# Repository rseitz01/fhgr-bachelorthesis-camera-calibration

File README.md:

# fhgr-bachelorthesis-camera-calibration

## Ordnerstruktur

- [`doc`](doc) Allgemeine Dokumentationen
- [`ledrunner`](ledrunner) Alles bezüglich STM32 (HW, SW, ...)
- [`src`](src) Source Codes (PC)

Die Veröffentlichung der Bachelorarbeit auf GitHub wurde durch den Dozenten und den Auftraggeber nach der Präsentation erlaubt.

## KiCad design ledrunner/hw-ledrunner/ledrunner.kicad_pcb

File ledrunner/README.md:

# ledrunner

## Ordnerstruktur

- [`housing-ledrunner`](housing-ledrunner) Komplettes Gehäuse für die Hardware
- [`hw-ledrunner`](hw-ledrunner) Schema + PCB der Hardware
- [`sw-camera-calibration`](sw-camera-calibration) STM32 Software (Prototyp der Kalibration)
- [`sw-ledrunner`](sw-ledrunner) STM32 Software zur Hardware

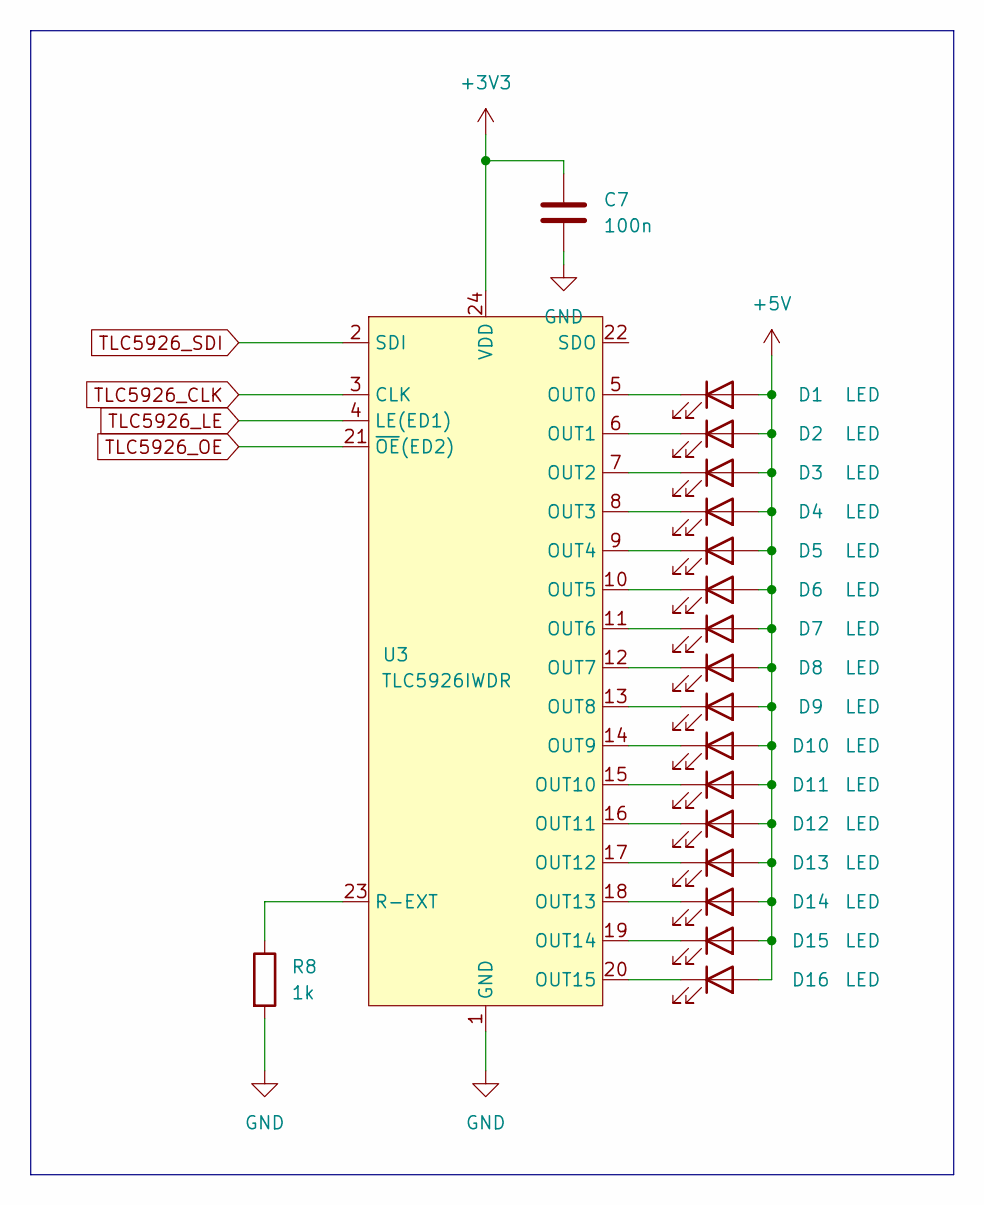
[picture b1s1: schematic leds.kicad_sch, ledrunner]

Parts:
C7: 100n; C_0603_1608Metric_Pad1.08x0.95mm_HandSolder
D1, D2, D3, D4, D5, D6, D7, D8, D9, D10, D11, D12, D13, D14, D15, D16: LED; LED_D5.0mm_FlatTop
R8: 1k; R_0603_1608Metric_Pad0.98x0.95mm_HandSolder
U3: TLC5926IWDR; SOIC-24W_7.5x15.4mm_P1.27mm

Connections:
+5V: D1.2 (A), D2.2 (A), D3.2 (A), D4.2 (A), D5.2 (A), D6.2 (A), D7.2 (A), D8.2 (A), D9.2 (A), D10.2 (A), D11.2 (A), D12.2 (A), D13.2 (A), D14.2 (A), D15.2 (A), D16.2 (A); also elsewhere on the board
GND: C7.2, R8.2, U3.1 (GND); also elsewhere on the board
unnamed: D1.1 (K), U3.5 (OUT0)
unnamed: D2.1 (K), U3.6 (OUT1)
unnamed: D3.1 (K), U3.7 (OUT2)
unnamed: D4.1 (K), U3.8 (OUT3)
unnamed: D5.1 (K), U3.9 (OUT4)
unnamed: D6.1 (K), U3.10 (OUT5)
unnamed: D7.1 (K), U3.11 (OUT6)
unnamed: D8.1 (K), U3.12 (OUT7)
unnamed: D9.1 (K), U3.13 (OUT8)
unnamed: D10.1 (K), U3.14 (OUT9)
unnamed: D11.1 (K), U3.15 (OUT10)
unnamed: D12.1 (K), U3.16 (OUT11)
unnamed: D13.1 (K), U3.17 (OUT12)
unnamed: D14.1 (K), U3.18 (OUT13)
unnamed: D15.1 (K), U3.19 (OUT14)
unnamed: D16.1 (K), U3.20 (OUT15)
unnamed: R8.1, U3.23 (R-EXT)
TLC5926_CLK: U3.3 (CLK); also elsewhere on the board
TLC5926_LE: U3.4 (LE(ED1)); also elsewhere on the board
TLC5926_OE: U3.21 (~OE(ED2)); also elsewhere on the board
TLC5926_SDI: U3.2 (SDI); also elsewhere on the board

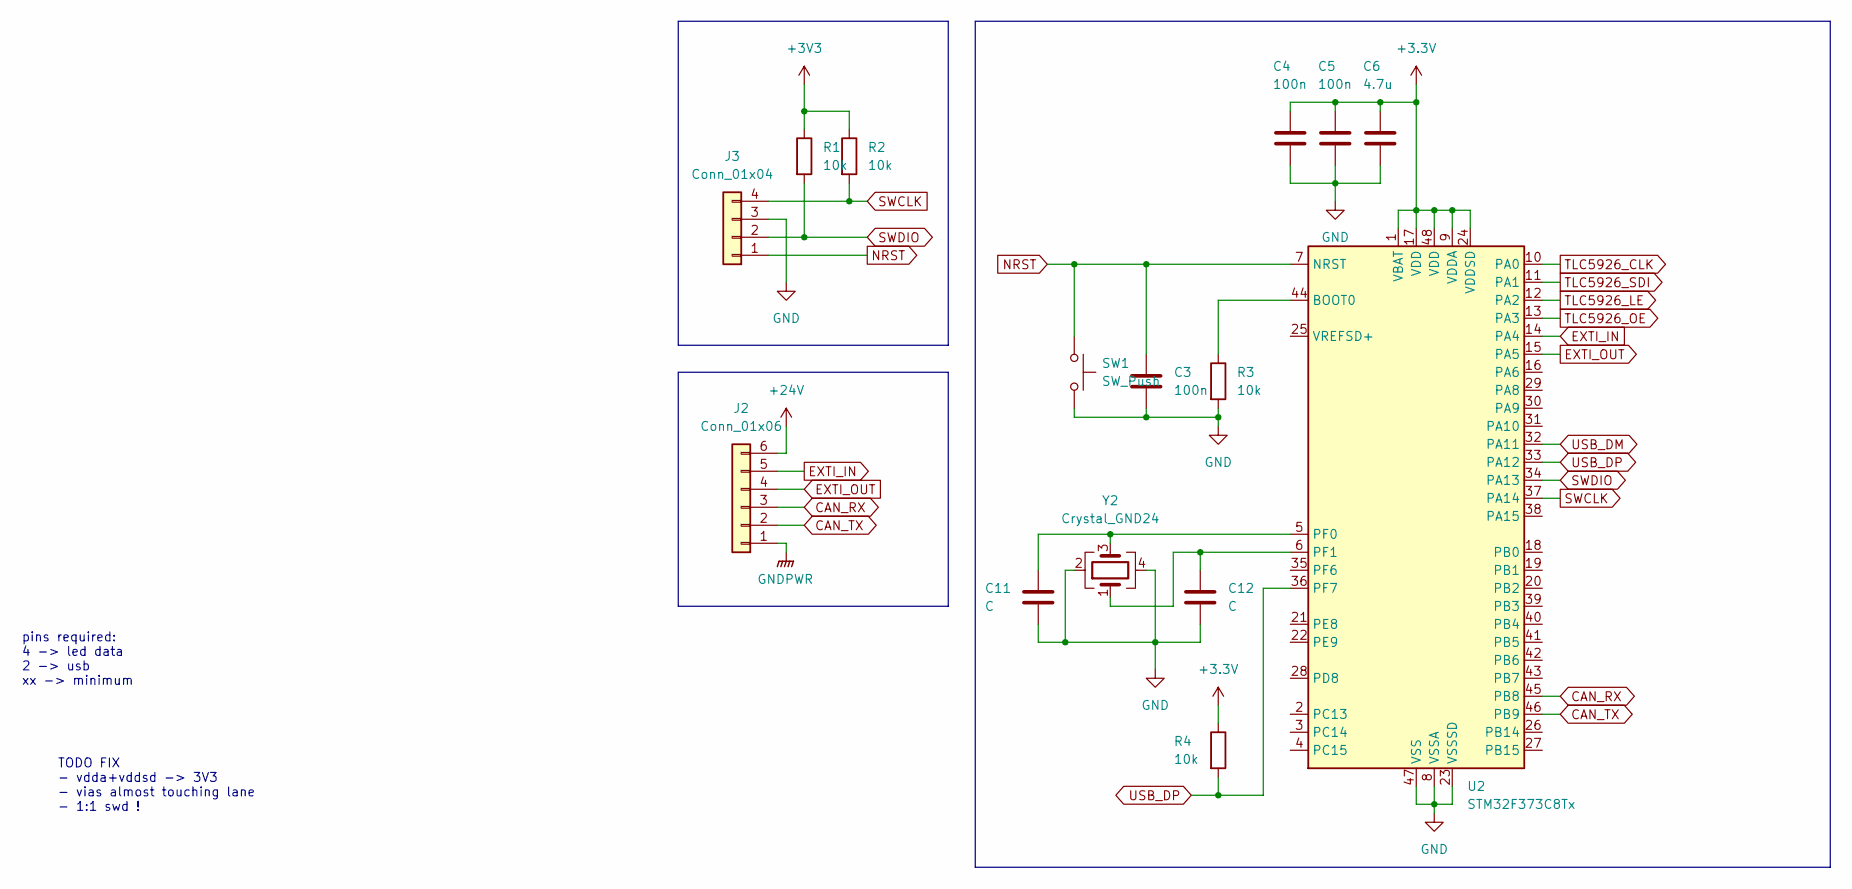
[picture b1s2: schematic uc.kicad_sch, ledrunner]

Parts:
C3, C4, C5: 100n; C_0603_1608Metric_Pad1.08x0.95mm_HandSolder
C6: 4.7u; C_0603_1608Metric_Pad1.08x0.95mm_HandSolder
C11, C12: C; C_0603_1608Metric_Pad1.08x0.95mm_HandSolder
J2: Conn_01x06; PinHeader_1x06_P2.54mm_Horizontal
J3: Conn_01x04; PinHeader_1x04_P2.54mm_Horizontal
R1, R2, R3, R4: 10k; R_0603_1608Metric_Pad0.98x0.95mm_HandSolder
SW1: SW_Push; SW_Push_1P1T_NO_6x6mm_H9.5mm
U2: STM32F373C8Tx; LQFP-48_7x7mm_P0.5mm
Y2: Crystal_GND24; Crystal_SMD_3225-4Pin_3.2x2.5mm

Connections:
+24V: J2.6; also elsewhere on the board
CAN_RX: J2.3, U2.45 (PB8)
CAN_TX: J2.2, U2.46 (PB9)
EXTI_IN: J2.5, U2.14 (PA4)
EXTI_OUT: J2.4, U2.15 (PA5)
GND: C3.2, C4.2, C5.2, C6.2, C11.2, C12.2, J3.3, R3.2, SW1.2, U2.8 (VSSA), U2.23 (VSSSD), U2.47 (VSS), Y2.2, Y2.4; also elsewhere on the board
GNDPWR: J2.1; also elsewhere on the board
NRST: C3.1, J3.1, SW1.1, U2.7 (NRST)
unnamed: R3.1, U2.44 (BOOT0)
unnamed: C11.1, U2.5 (PF0), Y2.3
unnamed: C12.1, U2.6 (PF1), Y2.1
SWCLK: J3.4, R2.2, U2.37 (PA14)
SWDIO: J3.2, R1.2, U2.34 (PA13)
TLC5926_CLK: U2.10 (PA0); also elsewhere on the board
TLC5926_LE: U2.12 (PA2); also elsewhere on the board
TLC5926_OE: U2.13 (PA3); also elsewhere on the board
TLC5926_SDI: U2.11 (PA1); also elsewhere on the board
USB_DM: U2.32 (PA11); also elsewhere on the board
USB_DP: R4.2, U2.33 (PA12), U2.36 (PF7); also elsewhere on the board

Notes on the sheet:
pins required: 4 -> led data 2 -> usb xx -> minimum
TODO FIX - vdda+vddsd -> 3V3 - vias almost touching lane - 1:1 swd !

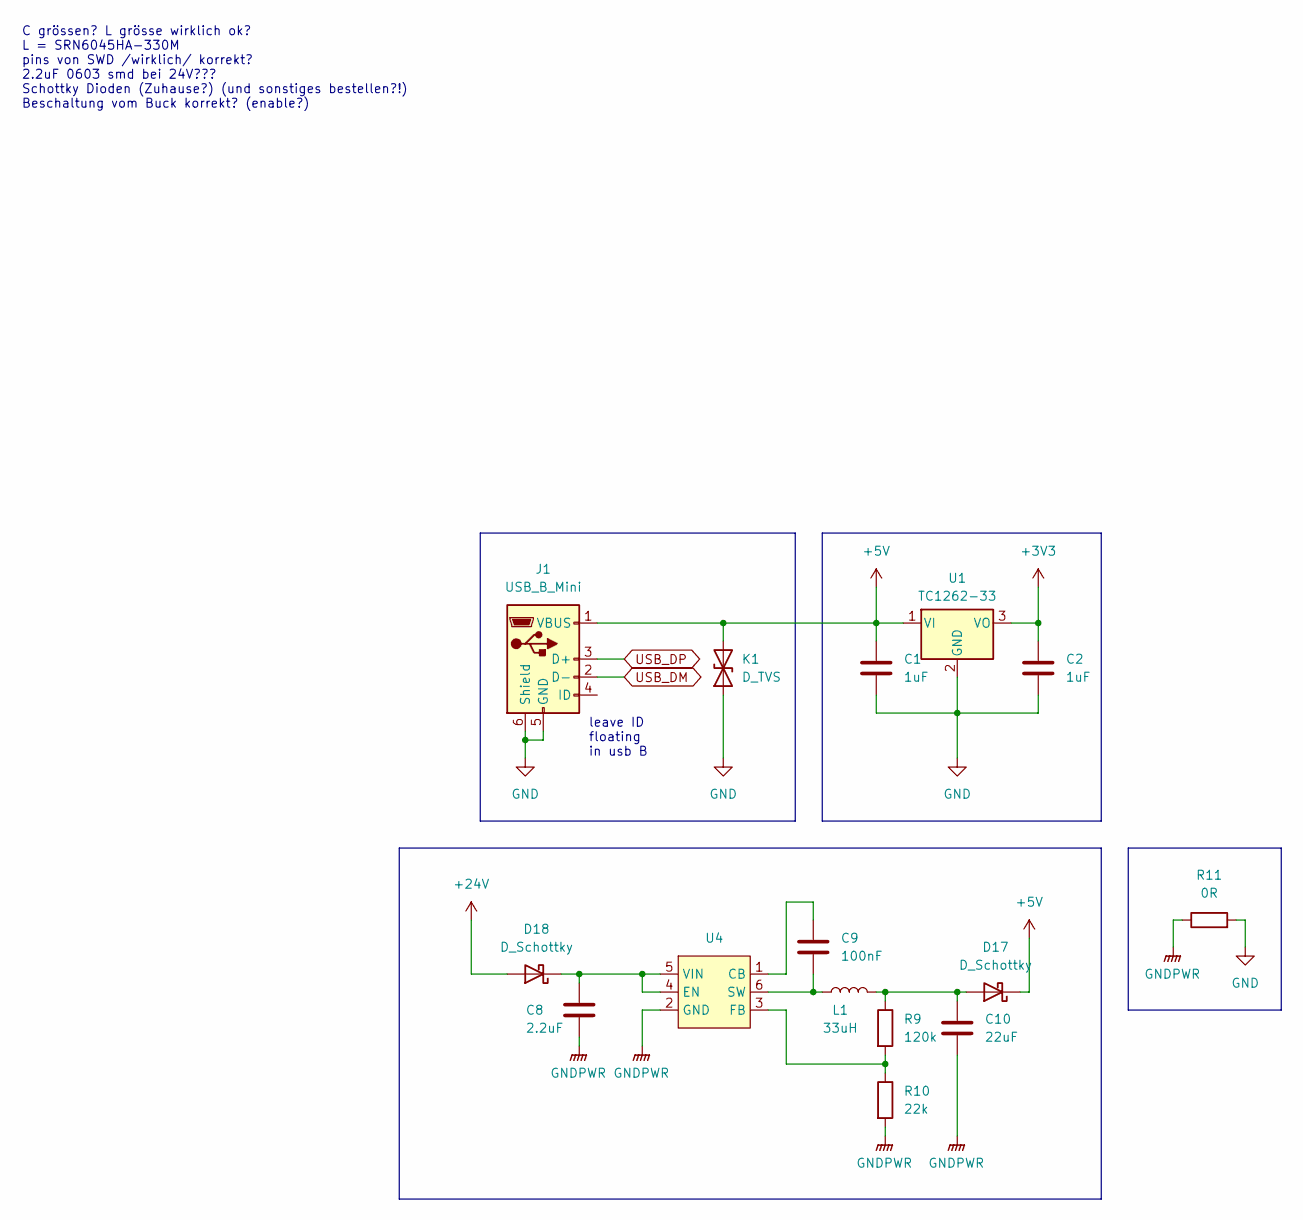
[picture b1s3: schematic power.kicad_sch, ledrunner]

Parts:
C1, C2: 1uF; C_0603_1608Metric_Pad1.08x0.95mm_HandSolder
C8: 2.2uF; C_0603_1608Metric_Pad1.08x0.95mm_HandSolder
C9: 100nF; C_0603_1608Metric_Pad1.08x0.95mm_HandSolder
C10: 22uF; C_Elec_5x5.4
D17, D18: D_Schottky; D_SMB
J1: USB_B_Mini; USB_Mini-B_Wuerth_65100516121_Horizontal
K1: D_TVS; D_SMB_Handsoldering
L1: 33uH; L_6.3x6.3_H3
R9: 120k; R_0603_1608Metric_Pad0.98x0.95mm_HandSolder
R10: 22k; R_0603_1608Metric_Pad0.98x0.95mm_HandSolder
R11: 0R; R_0603_1608Metric_Pad0.98x0.95mm_HandSolder
U1: TC1262-33; SOT-223-3_TabPin2
U4: SOT-23-6

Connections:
+5V: C1.1, D17.1 (K), J1.1 (VBUS), K1.2 (A2), U1.1 (VI); also elsewhere on the board
+24V: D18.2 (A); also elsewhere on the board
GND: C1.2, C2.2, J1.5 (GND), J1.6 (Shield), K1.1 (A1), R11.2, U1.2 (GND); also elsewhere on the board
GNDPWR: C8.2, C10.2, R10.2, R11.1, U4.2 (GND); also elsewhere on the board
unnamed: C10.1, D17.2 (A), L1.2, R9.1
unnamed: C8.1, D18.1 (K), U4.4 (EN), U4.5 (VIN)
unnamed: C9.1, U4.1 (CB)
unnamed: R9.2, R10.1, U4.3 (FB)
unnamed: C9.2, L1.1, U4.6 (SW)
USB_DM: J1.2 (D-); also elsewhere on the board
USB_DP: J1.3 (D+); also elsewhere on the board

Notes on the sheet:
C grössen? L grösse wirklich ok? L = SRN6045HA-330M pins von SWD /wirklich/ korrekt? 2.2uF 0603 smd bei 24V??? Schottky Dioden (Zuhause?) (und sonstiges bestellen?!) Beschaltung vom Buck korrekt? (enable?)
leave ID floating in usb B

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
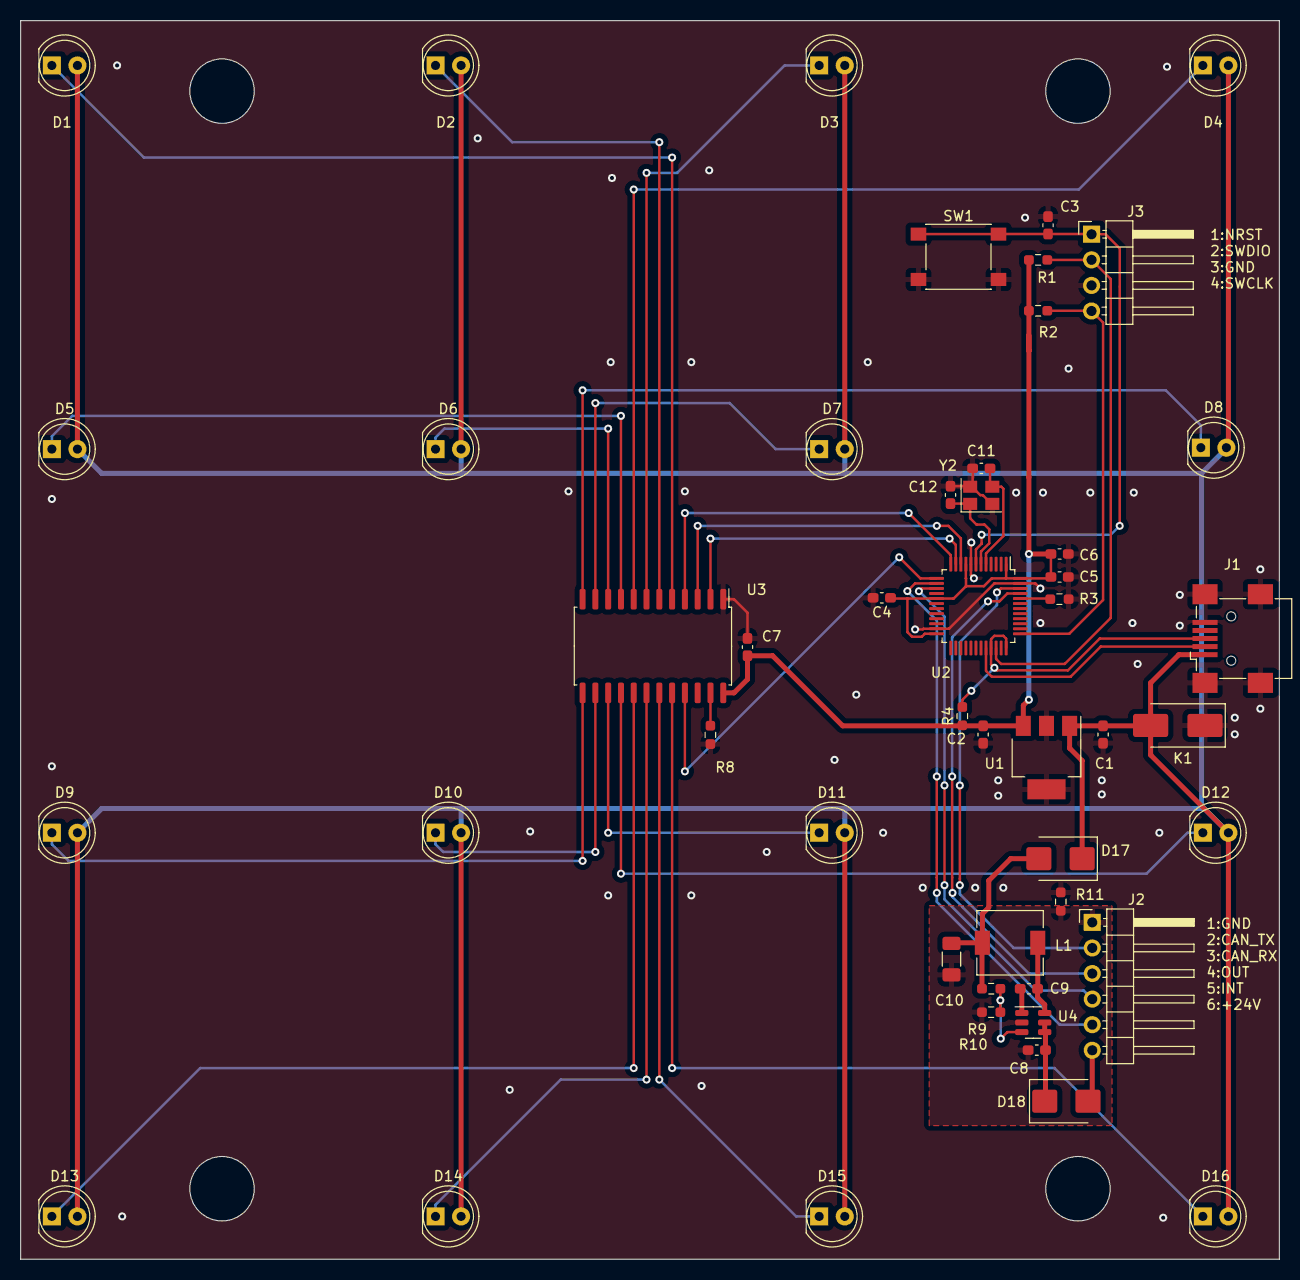
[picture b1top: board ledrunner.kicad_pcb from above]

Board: 2 copper layers, 125.0 x 123.0 mm, 49 parts (0 on the bottom side), 43 nets.

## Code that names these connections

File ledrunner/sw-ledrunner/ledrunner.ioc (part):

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Mcu.Name=STM32F373C(8-B-C)Tx
Mcu.Package=LQFP48
Mcu.UserName=STM32F373CBTx
PA0.GPIOParameters=GPIO_Speed,GPIO_Label
PA0.GPIO_Label=TLC5926_CLK
PA0.GPIO_Speed=GPIO_SPEED_FREQ_HIGH
PA0.Signal=GPIO_Output
PA1.GPIOParameters=GPIO_Speed,GPIO_Label
PA1.GPIO_Label=TLC5926_SDI
PA1.GPIO_Speed=GPIO_SPEED_FREQ_HIGH
PA1.Signal=GPIO_Output
PA11.GPIOParameters=GPIO_PuPd
PA11.GPIO_PuPd=GPIO_NOPULL
PA11.Mode=Device
PA11.Signal=USB_DM
PA12.GPIOParameters=GPIO_PuPd
PA12.GPIO_PuPd=GPIO_PULLUP
PA12.Mode=Device
PA12.Signal=USB_DP
PA13.Mode=Serial_Wire
PA13.Signal=SYS_JTMS-SWDIO
PA14.Mode=Serial_Wire
PA14.Signal=SYS_JTCK-SWCLK
PA2.GPIOParameters=GPIO_Speed,GPIO_Label
PA2.GPIO_Label=TLC5926_LE
PA2.GPIO_Speed=GPIO_SPEED_FREQ_HIGH
PA2.Signal=GPIO_Output
PA3.GPIOParameters=GPIO_Speed,GPIO_Label
PA3.GPIO_Label=TLC5926_OE
PA3.GPIO_Speed=GPIO_SPEED_FREQ_HIGH
PA3.Signal=GPIO_Output
PA4.GPIOParameters=GPIO_Label
PA4.GPIO_Label=GPIO_Int
PA4.Signal=GPXTI4
PA5.GPIOParameters=GPIO_Label
PA5.GPIO_Label=GPIO_Out
PA5.Signal=GPIO_Output
PB8.Mode=CAN_Activate
PB8.Signal=CAN_RX
PB9.Mode=CAN_Activate
PB9.Signal=CAN_TX
PF0-OSC_IN.Mode=HSE-External-Oscillator
PF0-OSC_IN.Signal=RCC_OSC_IN
PF1-OSC_OUT.Mode=HSE-External-Oscillator
PF1-OSC_OUT.Signal=RCC_OSC_OUT
PF7.GPIOParameters=PinState,GPIO_PuPd,GPIO_Label,GPIO_ModeDefaultOutputPP
PF7.GPIO_Label=USB_Reconnect
PF7.GPIO_ModeDefaultOutputPP=GPIO_MODE_OUTPUT_OD
PF7.GPIO_PuPd=GPIO_NOPULL
PF7.PinState=GPIO_PIN_RESET
PF7.Signal=GPIO_Output
RCC.HSEPLLFreq_Value=24000000
RCC.HSE_VALUE=24000000
RCC.SYSCLKFreq_VALUE=72000000
RCC.SYSCLKSource=RCC_SYSCLKSOURCE_PLLCLK
board=custom

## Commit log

2024-09-04 let there be light...
2024-09-04 mupdf wants to repair this
2024-10-15 let there be light again
2024-10-15 don't need these
2024-10-15 also don't need here
